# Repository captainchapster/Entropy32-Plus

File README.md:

# Entropy32 Plus

**Entropy32** (aka *The Universe Bifurcator*) is a dedicated Bitcoin seed phrase generator that uses radioactive decay as its entropy source. It's completely open source and designed to be simple, auditable, and buildable by anyone with readily available components.

## Why radioactive decay?

Pseudo-random number generators are deterministic — given the same seed, they always produce the same output. True randomness for something as consequential as a Bitcoin wallet's seed phrase should come from a physical process nobody can predict or manipulate. Radioactive decay is quantum-mechanically random: the timing of individual decay events is fundamentally unpredictable, making it an ideal entropy source for generating cryptographic secrets.

## How it works

1. A Geiger counter detects decay events from a radioactive source (or background) and outputs a pulse via a 3.5mm audio jack.

2. An LM393 comparator IC then takes the 0-1.5V pulse and compares it to a bias of ~0.5V via a voltage divider such that if V>0.5V we get HIGH else LOW.

3. The timing between events is captured and compared in non-overlapping pairs (each inter-arrival time feeds exactly one comparison, so adjacent output bits never share an input interval). Each resulting bit passes two continuous NIST SP 800-90B health tests (Repetition Count Test and Adaptive Proportion Test) before it's fed through SHA-256 conditioning to whiten the raw entropy and remove any bias — if either test trips, the device halts rather than generating a seed from a degraded source.
4. The conditioned entropy is mapped to words from the standard BIP39 English wordlist.
5. A simple button-driven, state-machine UI walks you through generating and displaying your seed phrase — entirely offline, with no wireless connectivity, no persistent storage of the seed, and no software dependencies beyond the device itself.

## How long does it take to generate a seed?

The firmware always fills a 512-bit raw pool before conditioning — that's true whether you pick a 12-word or 24-word phrase, since the seed length only changes how many of the whitened bits get used afterward, not how much raw entropy gets collected. Because of the non-overlapping interval pairing described above, each output bit costs two Geiger pulses, so at a steady count rate the pool fills in roughly:

```
minutes ≈ 1024 / CPM
```

The device's collection screen shows live CPM and a running ETA using this same math, so you don't need to do it by hand. Actual CPM depends heavily on your specific tube, source activity, distance, and shielding — treat the table below as a rough guide, not a spec, and follow appropriate safety/legal practices for any check source you use:

| Source | Typical CPM | Time to fill the pool |
|---|---|---|
| Ambient background | ~15–25 CPM | ~40–70 min |
| Uranium glass ("vaseline glass") | ~50–100 CPM | ~10–20 min |
| Thoriated tungsten welding rod (2% ThO₂) | ~100–200 CPM | ~5–10 min |
| Am-241 foil (smoke detector ionization chamber) | ~300–800 CPM | ~1.3–3.5 min |
| Low-activity calibration/check source | ~1,000–3,000 CPM | ~20 sec–1 min |
| High-activity check source (close contact) | ~5,000–10,000+ CPM | ~6–12 sec |

## Hardware

- Custom PCB built around an [ATmega328P microcontroller](https://ww1.microchip.com/downloads/en/DeviceDoc/Atmel-7810-Automotive-Microcontrollers-ATmega328P_Datasheet.pdf), designed in [KiCad](https://www.kicad.org/)
- Geiger counter module as the entropy source (currently designed to take the 3.5mm output of the [GQ Electronics GMC-320S](https://www.gqelectronicsllc.com/comersus/store/comersus_viewItem.asp?idProduct=5787))
- [LM393 comparator IC](https://www.ti.com/product/LM393)
- Push-button interface for on-device operation
- Serveral common passives i.e. resistors, capacitors, and LEDs
- 16MHZ crystal oscillator
- 0.91" OLED display with I2C adaptor
- PJ320E 3.5mm audio jack
- USB-C receptacle 6 pin
- header pins

## 3D printed case

I have included a custom designed basic case which you can 3d print to protect your device. The design works by allowing the board to slide on tracks into the case, once inserted all the way, a small prong prevents the board from sliding back out. If you plan to use this case be sure to hold the board down while unplugging the USB and/or the 3.5mm audio cable as this would otherwise put excessive strain on the prong to the point it may break off and fail. 

## Repository contents

| File | Purpose |
|---|---|
| `entropy32_plus.ino` | Main firmware — state machine, entropy capture, and UI logic |
| `sha256.h` / `sha256.cpp` | SHA-256 implementation used to condition raw entropy |
| `bip39_wordlist.h` | BIP39 English wordlist, compiled into firmware |
| `button.h` | Button input handling |
| `logo_bitmap.h` | Boot splash bitmap, compiled into firmware |
| `tools/english.txt` | Source BIP39 wordlist |
| `tools/generate_wordlist.py` | Script to regenerate `bip39_wordlist.h` from `english.txt` |
| `tools/generate_logo_bitmap.py` | Script to regenerate `logo_bitmap.h` from a rendered image |
| `KiCad/...` | Schematics, PCB and other files |
| `KiCad/production/...` | Fabrication data: bom, zipped fab files, and positions etc |
| `enclosures/...` | 3D print files for cases & enclosures |

## Building it yourself

The Arduino sketch (`entropy32_plus.ino`) and its accompanying `.h`/`.cpp` files must remain in the same top-level folder for the Arduino IDE to compile correctly — it doesn't recurse into subfolders for sketch code. Open `entropy32_plus.ino` in the Arduino IDE, verify your board settings for the ATmega328P, and flash as normal.

Use the KiCad files to tailor the board to your liking before fabrication or use the premade production files to order your board and/or pick and place from your preferred fabrication plant i.e. JLCPCB or PCB Way etc.

### Programming a bare ATmega328P

A freshly fabricated board has a blank ATmega328P — there's no bootloader on it and no USB-to-serial chip to flash it through, so the usual "select a port and hit upload" Arduino flow doesn't apply until it's been programmed once via the ICSP header exposed on the board.

1. **Wire up an ISP programmer.** Either a second Arduino running the `ArduinoISP` example sketch, or a dedicated programmer such as a USBasp, connected to the ICSP header. If using a USBasp, make sure it's set to 5V logic to match this board.
2. **Burn the bootloader.** In the Arduino IDE, select **Arduino Uno** or **Arduino Nano** as the board type (either is a stand-in for a bare ATmega328P at this stage), select your ISP programmer under Tools → Programmer, and run **Tools → Burn Bootloader**. This also sets the fuses for running off the board's 16MHz external crystal rather than the internal oscillator.
3. **Flash the firmware.** With the bootloader in place and the board running at 16MHz external clock, open `entropy32_plus.ino` and upload it via **Sketch → Upload Using Programmer** (still through the same ISP connection — the board has no onboard USB-serial chip for a normal serial upload).

## Flash footprint

Geiger pulse capture, the SP 800-90B runtime health tests, SHA-256 conditioning, the full BIP39 wordlist, the OLED driver, and the entire menu/boot UI all fit on the ATmega328P's 32KB of flash — with 486 bytes to spare:

```
Sketch uses 30234 bytes (98%) of program storage space. Maximum is 30720 bytes.
Global variables use 1061 bytes (51%) of dynamic memory, leaving 987 bytes for local variables. Maximum is 2048 bytes.
```

Breakdown of where it all goes, pulled from the compiled `.elf` with `avr-size`/`avr-nm`:

| Symbol | Bytes | What it is |
|---|---|---|
| `BIP39_WORDLIST_BLOB` | 13,117 | The official 2048-word BIP39 English wordlist |
| `main` (loop + inlined UI code) | 3,062 | State machine, screen drawing, menu logic |
| `SHA256::transform` | 2,278 | The SHA-256 compression function |
| `vfprintf` | 948 | Pulled in by `snprintf`, used for CPM/ETA/progress formatting |
| `u8x8_font_5x7_r` | 764 | Built-in OLED font glyph table |
| U8x8 / TwoWire internals | ~1,100 | I2C + SSD1306 driver plumbing |
| `LOGO_BITMAP` | 384 | Boot splash bitmap |
| `K` (SHA-256 round constants) | 256 | Fixed SHA-256 round constants |

The wordlist alone is 43% of the chip. Adafruit_GFX + Adafruit_SSD1306 don't fit alongside it — see the note in `entropy32_plus.ino` — which is why the firmware talks to the display through U8x8's text-only mode instead.

## Validation

The firmware runs the two minimal continuous health tests NIST SP 800-90B requires of a noise source at runtime — a Repetition Count Test and an Adaptive Proportion Test (see `runHealthChecks()` in `entropy32_plus.ino`) — which will halt the device rather than generate a seed if the raw source looks stuck or degraded. Runtime health tests are not the same as validating the source's entropy.

### Full-length entropy assessment (2,000,000 edges)

A 23-day capture (2026-10-03 to 2026-10-26) was logged with [Entropy32 Recorder](https://github.com/captainchapster/Entropy32-Recorder). The recorder is a separate board that timestamps the same post-LM393 D2 rising edges the firmware reads. It captured 2,000,000 edges (~61 CPM average) with zero buffer overruns or transport drops. The source was a GMC-320S Geiger counter beside a glass jar of cut-up 2% thoriated tungsten welding electrodes, on top of background radiation.

The intervals were put through the firmware's exact bit derivation from this repository at `2b9893a`: 200 µs minimum interval, non-overlapping pairs and ties discarded. No intervals fell under the 200 µs cutoff (the detector's dead time is ~750 µs) and there were no ties. That produced 999,999 comparison bits (500,205 zeros, 499,794 ones, within 0.4 standard deviations of a fair coin). Those bits were assessed with NIST's [`ea_non_iid`](https://github.com/usnistgov/SP800-90B_EntropyAssessment) (v1.1.8):

| Estimator | Min-entropy (bits per bit) |
|---|---|
| Most Common Value | 0.996 |
| Collision | 0.885 |
| Markov | 0.996 |
| Compression | **0.828** |
| t-Tuple | 0.895 |
| LRS | 0.984 |
| MultiMCW prediction | 0.996 |
| Lag prediction | 0.998 |
| MultiMMC prediction | 0.983 |
| LZ78Y prediction | 0.983 |

The assessed min-entropy is the lowest of these: **H ≈ 0.828 bits per comparison bit**, set by the compression estimator. At that rate, the 512-bit raw pool holds about 424 bits of min-entropy before SHA-256 conditioning. That is well above the 256 bits a 24-word phrase needs.

What this does and doesn't show:

- **The dataset is one bit short of the 1,000,000-sample size.** 2,000,000 edges give 1,999,999 intervals and so 999,999 non-overlapping pairs. `ea_non_iid` prints a warning about it, and the recorder's `verify_evidence.py` therefore labels the package a pilot. The missing sample makes no practical difference to the estimates, but the recorder now stops captures on the comparison-bit count so the next run will clear the threshold.
- Only the sequential-dataset non-IID estimators were run. The SP 800-90B restart tests were not.
- It covers one device, one Geiger tube, one source and one environment. The enriched source ran at ~61 CPM; a background-only setup is slower, and this run says nothing about other builds or sources.
- It is an entropy assessment, not NIST certification or formal validation.

The raw edges, derived bits, full tool output, manifest and SHA-256 checksums are all published in the [evidence directory](https://github.com/captainchapster/Entropy32-Recorder/tree/d126967329e564d2764d65eb4a7c00ae7588aace/entropy32_sp80090b_2026-10-03a). Running `python tools/verify_evidence.py entropy32_sp80090b_2026-10-03a` in that repository re-derives the bits from the raw edges and checks every count and hash.

### Earlier pilot (10,000 edges)

Before the full-length run, a 10-hour pilot captured 10,000 edges (~17 CPM) and was derived with this repository at `311c859`. That produced 4,999 comparison bits (2,543 zeros, 2,456 ones). `ea_non_iid` assessed them at **H ≈ 0.738 bits per comparison bit** (collision estimator; compression was not run at that size). That is lower than the full-length result because the estimators' 99% confidence bounds are wide with so few samples. The source and setup details for that run were not recorded. Its [evidence directory](https://github.com/captainchapster/Entropy32-Recorder/tree/1d47487bc94c2b7c9baa2feec54d4443b60ba87c/entropy32_sp80090b_2026-09-22a) is kept for reference.

Please verify the entropy source you intend to use; otherwise, understand that you are using the device at your own risk.

## Disclaimer

This is a hobbyist/educational project. If you use it to generate a real Bitcoin seed phrase, understand the risks: verify the entropy quality yourself, review the code, and never trust a seed-generating device (this one included) with significant funds without independent auditing.

## Licenses

- For firmware/software, see [`MIT LICENSE`](./LICENSE).
- For hardware, see [`CERN-OHL-S v2 LICENSE`](./LICENSE-HARDWARE).

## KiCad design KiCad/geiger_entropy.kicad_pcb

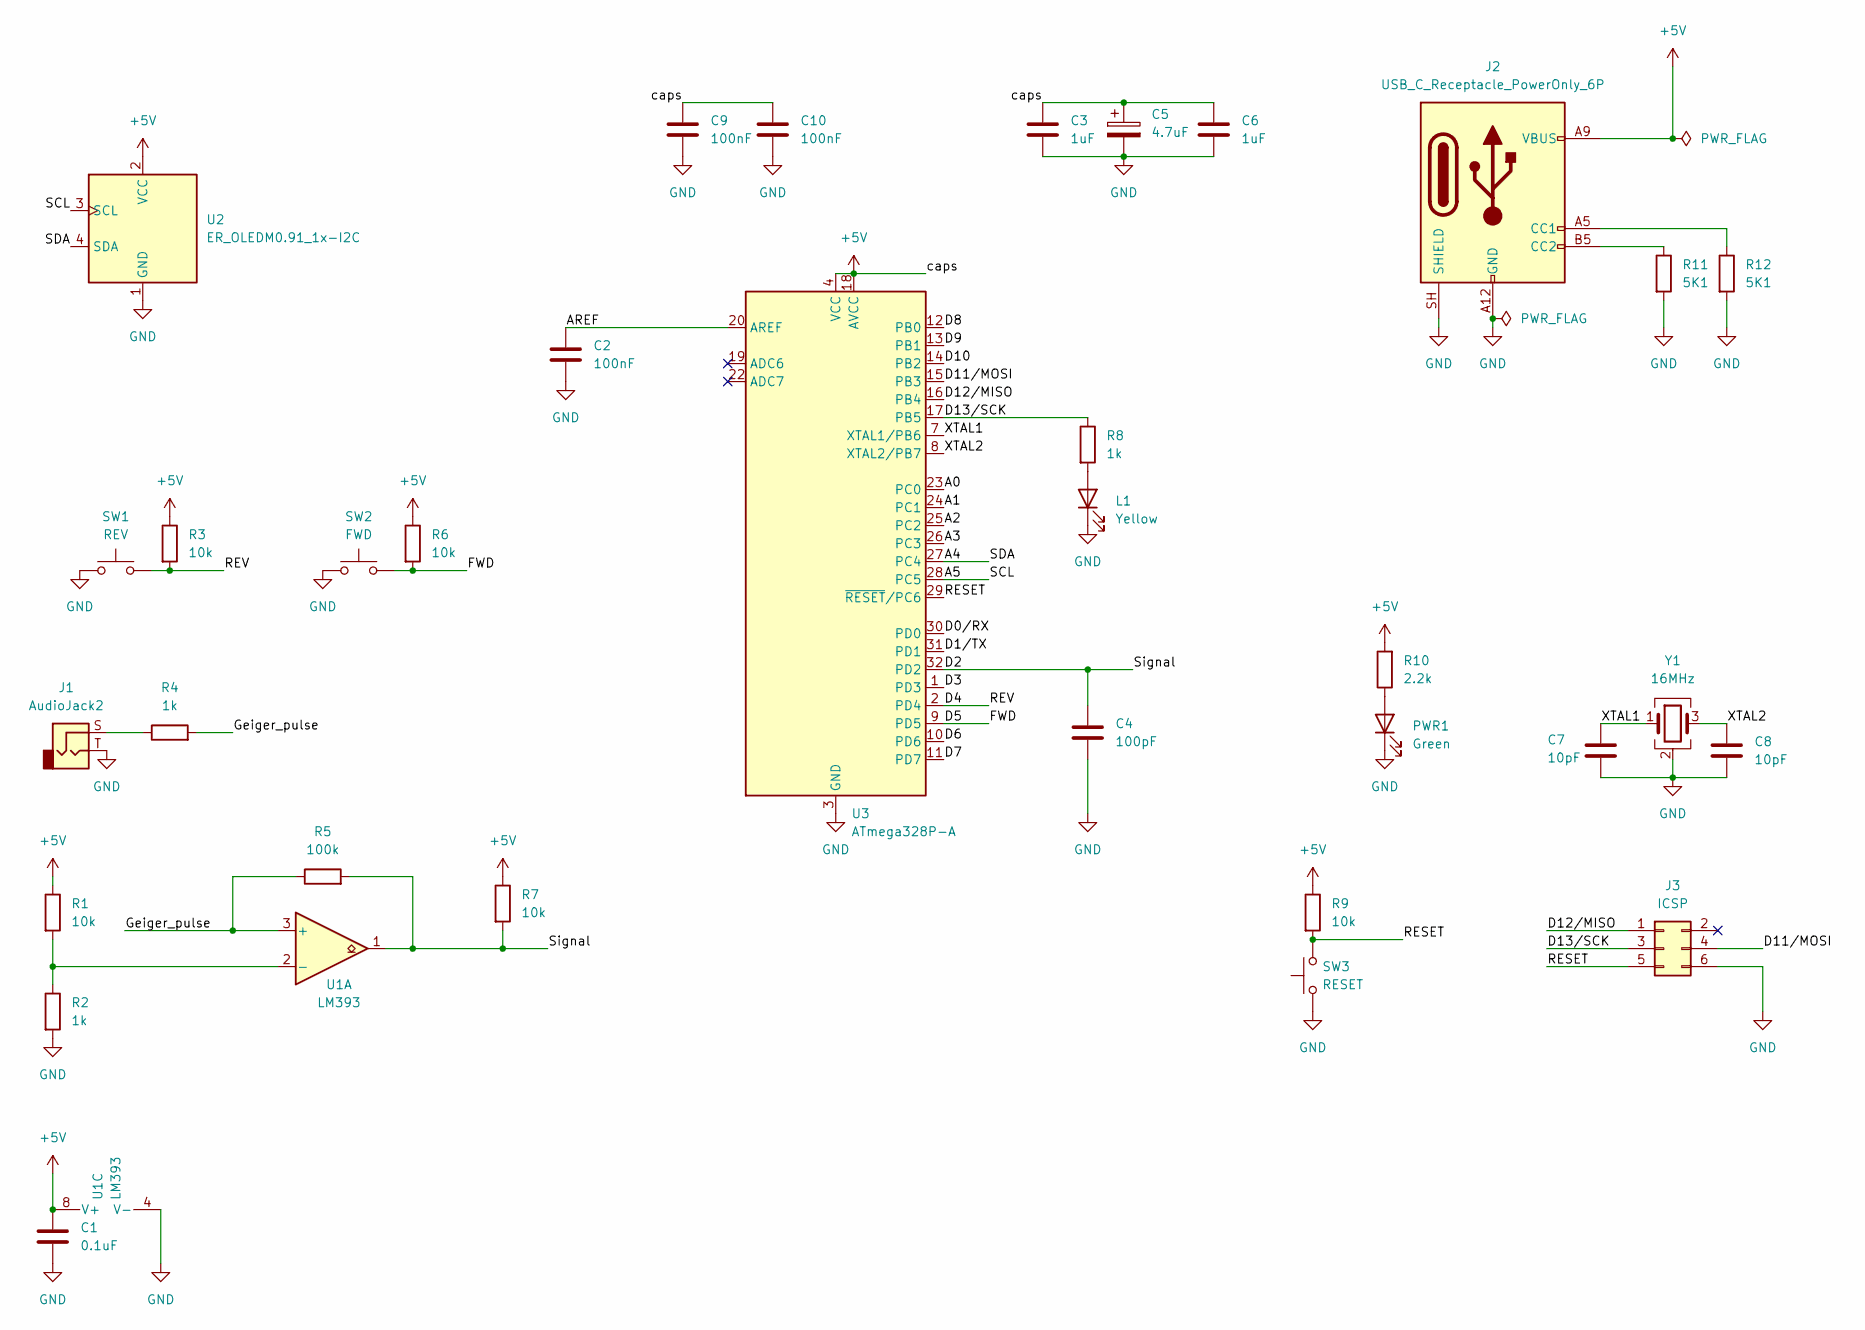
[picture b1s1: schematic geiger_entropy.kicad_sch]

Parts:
C1: 0.1uF; C_0805_2012Metric
C2, C9, C10: 100nF; C_0805_2012Metric
C3, C6: 1uF; C_0805_2012Metric
C4: 100pF; C_0805_2012Metric
C5: 4.7uF; CP_Elec_5x3
C7, C8: 10pF; C_0805_2012Metric
J1: AudioJack2; Jack_3.5mm_PJ320E_Horizontal
J2: USB_C_Receptacle_PowerOnly_6P; USB_C_Receptacle_GCT_USB4125-xx-x_6P_TopMnt_Horizontal
J3: ICSP; PinHeader_2x03_P2.54mm_Vertical
L1: Yellow; LED_0805_2012Metric
PWR1: Green; LED_0805_2012Metric
R1, R3, R6, R7, R9: 10k; R_0805_2012Metric
R2, R4, R8: 1k; R_0805_2012Metric
R5: 100k; R_0805_2012Metric
R10: 2.2k; R_0805_2012Metric
R11, R12: 5K1; R_0805_2012Metric
SW1: REV; SW_PUSH_6mm
SW2: FWD; SW_PUSH_6mm
SW3: RESET; SW_PUSH_6mm
U1: LM393; SOIC-8_3.9x4.9mm_P1.27mm
U2: ER_OLEDM0.91_1x-I2C
U3: ATmega328P-A; TQFP-32_7x7mm_P0.8mm
Y1: 16MHz; Crystal_SMD_2520-4Pin_2.5x2.0mm

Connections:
+5V: C1.1, C3.1, C5.1, C6.1, C9.1, C10.1, J2.A9 (VBUS), J2.B9 (VBUS), R1.1, R3.1, R6.1, R7.1, R9.1, R10.2, U1.8 (V+), U2.2 (VCC), U3.4 (VCC), U3.6 (VCC), U3.18 (AVCC)
/A0: U3.23 (PC0)
/A1: U3.24 (PC1)
/A2: U3.25 (PC2)
/A3: U3.26 (PC3)
/A4: U2.4 (SDA), U3.27 (PC4)
/A5: U2.3 (SCL), U3.28 (PC5)
/AREF: C2.1, U3.20 (AREF)
/D0/RX: U3.30 (PD0)
/D1/TX: U3.31 (PD1)
/D2: C4.1, R5.2, R7.2, U1.1, U3.32 (PD2)
/D3: U3.1 (PD3)
/D4: R3.2, SW1.2, U3.2 (PD4)
/D5: R6.2, SW2.2, U3.9 (PD5)
/D6: U3.10 (PD6)
/D7: U3.11 (PD7)
/D8: U3.12 (PB0)
/D9: U3.13 (PB1)
/D10: U3.14 (PB2)
/D11/MOSI: J3.4, U3.15 (PB3)
/D12/MISO: J3.1, U3.16 (PB4)
/D13/SCK: J3.3, R8.1, U3.17 (PB5)
/Geiger_pulse: R4.2, R5.1, U1.3 (+)
/RESET: J3.5, R9.2, SW3.2, U3.29 (~RESET/PC6)
/XTAL1: C7.1, U3.7 (XTAL1/PB6), Y1.1
/XTAL2: C8.1, U3.8 (XTAL2/PB7), Y1.3
GND: C1.2, C2.2, C3.2, C4.2, C5.2, C6.2, C7.2, C8.2, C9.2, C10.2, J1.T, J2.A12 (GND), J2.B12 (GND), J2.SH (SHIELD), J3.6, L1.1 (K), PWR1.1 (K), R2.2, R11.2, R12.2, SW1.1, SW2.1, SW3.1, U1.4 (V-), U2.1 (GND), U3.3 (GND), U3.5 (GND), U3.21 (GND), Y1.2 (G), Y1.4 (G)
unnamed: J1.S, R4.1
unnamed: J2.A5 (CC1), R12.1
unnamed: J2.B5 (CC2), R11.1
unnamed: L1.2 (A), R8.2
unnamed: PWR1.2 (A), R10.1
unnamed: R1.2, R2.1, U1.2 (-)

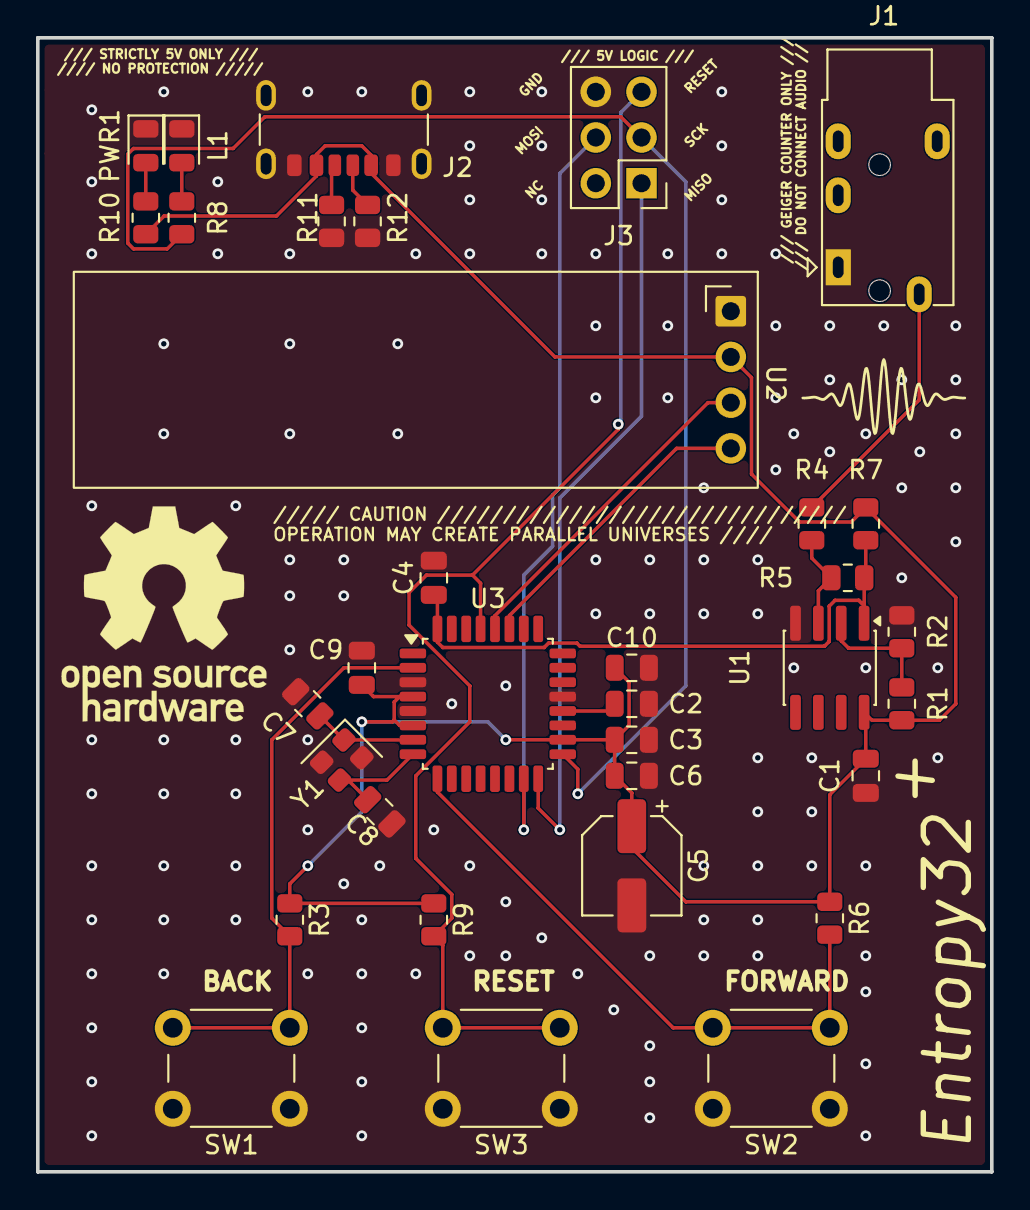
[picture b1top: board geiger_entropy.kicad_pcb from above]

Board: 2 copper layers, 53.0 x 63.0 mm, 34 parts (0 on the bottom side), 21 nets.

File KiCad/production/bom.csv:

Designator,Footprint,Quantity,Value,LCSC Part #
C1,0805,1,0.1uF,
"C10, C2, C9",0805,3,100nF,
"C3, C6",0805,2,1uF,
C4,0805,1,100pF,
C5,CP_Elec_5x3,1,4.7uF,
"C7, C8",0805,2,10pF,
J1,Jack_3.5mm_PJ320E_Horizontal,1,AudioJack2,
J2,USB_C_Receptacle_GCT_USB4125-xx-x_6P_TopMnt_Horizontal,1,USB_C_Receptacle_PowerOnly_6P,
J3,PinHeader_2x03_P2.54mm_Vertical,1,ICSP,
L1,0805,1,Yellow,
PWR1,0805,1,Green,
"R1, R3, R6, R7, R9",0805,5,10k,
R10,0805,1,2.2k,
"R11, R12",0805,2,5K1,
"R2, R4, R8",0805,3,1k,
R5,0805,1,100k,
SW1,SW_PUSH_6mm,1,REV,
SW2,SW_PUSH_6mm,1,FWD,
SW3,SW_PUSH_6mm,1,RESET,
U1,SOIC-8_3.9x4.9mm_P1.27mm,1,LM393,
U2,ER_OLEDM0.91_1x-I2C,1,ER_OLEDM0.91_1x-I2C,
U3,TQFP-32_7x7mm_P0.8mm,1,ATmega328P-A,
Y1,Crystal_SMD_2520-4Pin_2.5x2.0mm,1,16MHz,
